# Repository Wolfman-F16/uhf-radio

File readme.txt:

This file is part of uhf-radio.
This project is hosted on github.com/Wolfman-F16
uhf-radio uses v-usb, which comes with its own GPL v2 license (see /usbdrv/license.txt).

    uhf-radio is free software: you can redistribute it and/or modify
    it under the terms of the GNU General Public License as published by
    the Free Software Foundation, either version 2 of the License, or
    any later version.

    uhf-radio is distributed in the hope that it will be useful,
    but WITHOUT ANY WARRANTY; without even the implied warranty of
    MERCHANTABILITY or FITNESS FOR A PARTICULAR PURPOSE.  See the
    GNU General Public License for more details.

    You should have received a copy of the GNU General Public License
    along with uhf-radio.  If not, see <http://www.gnu.org/licenses/>.

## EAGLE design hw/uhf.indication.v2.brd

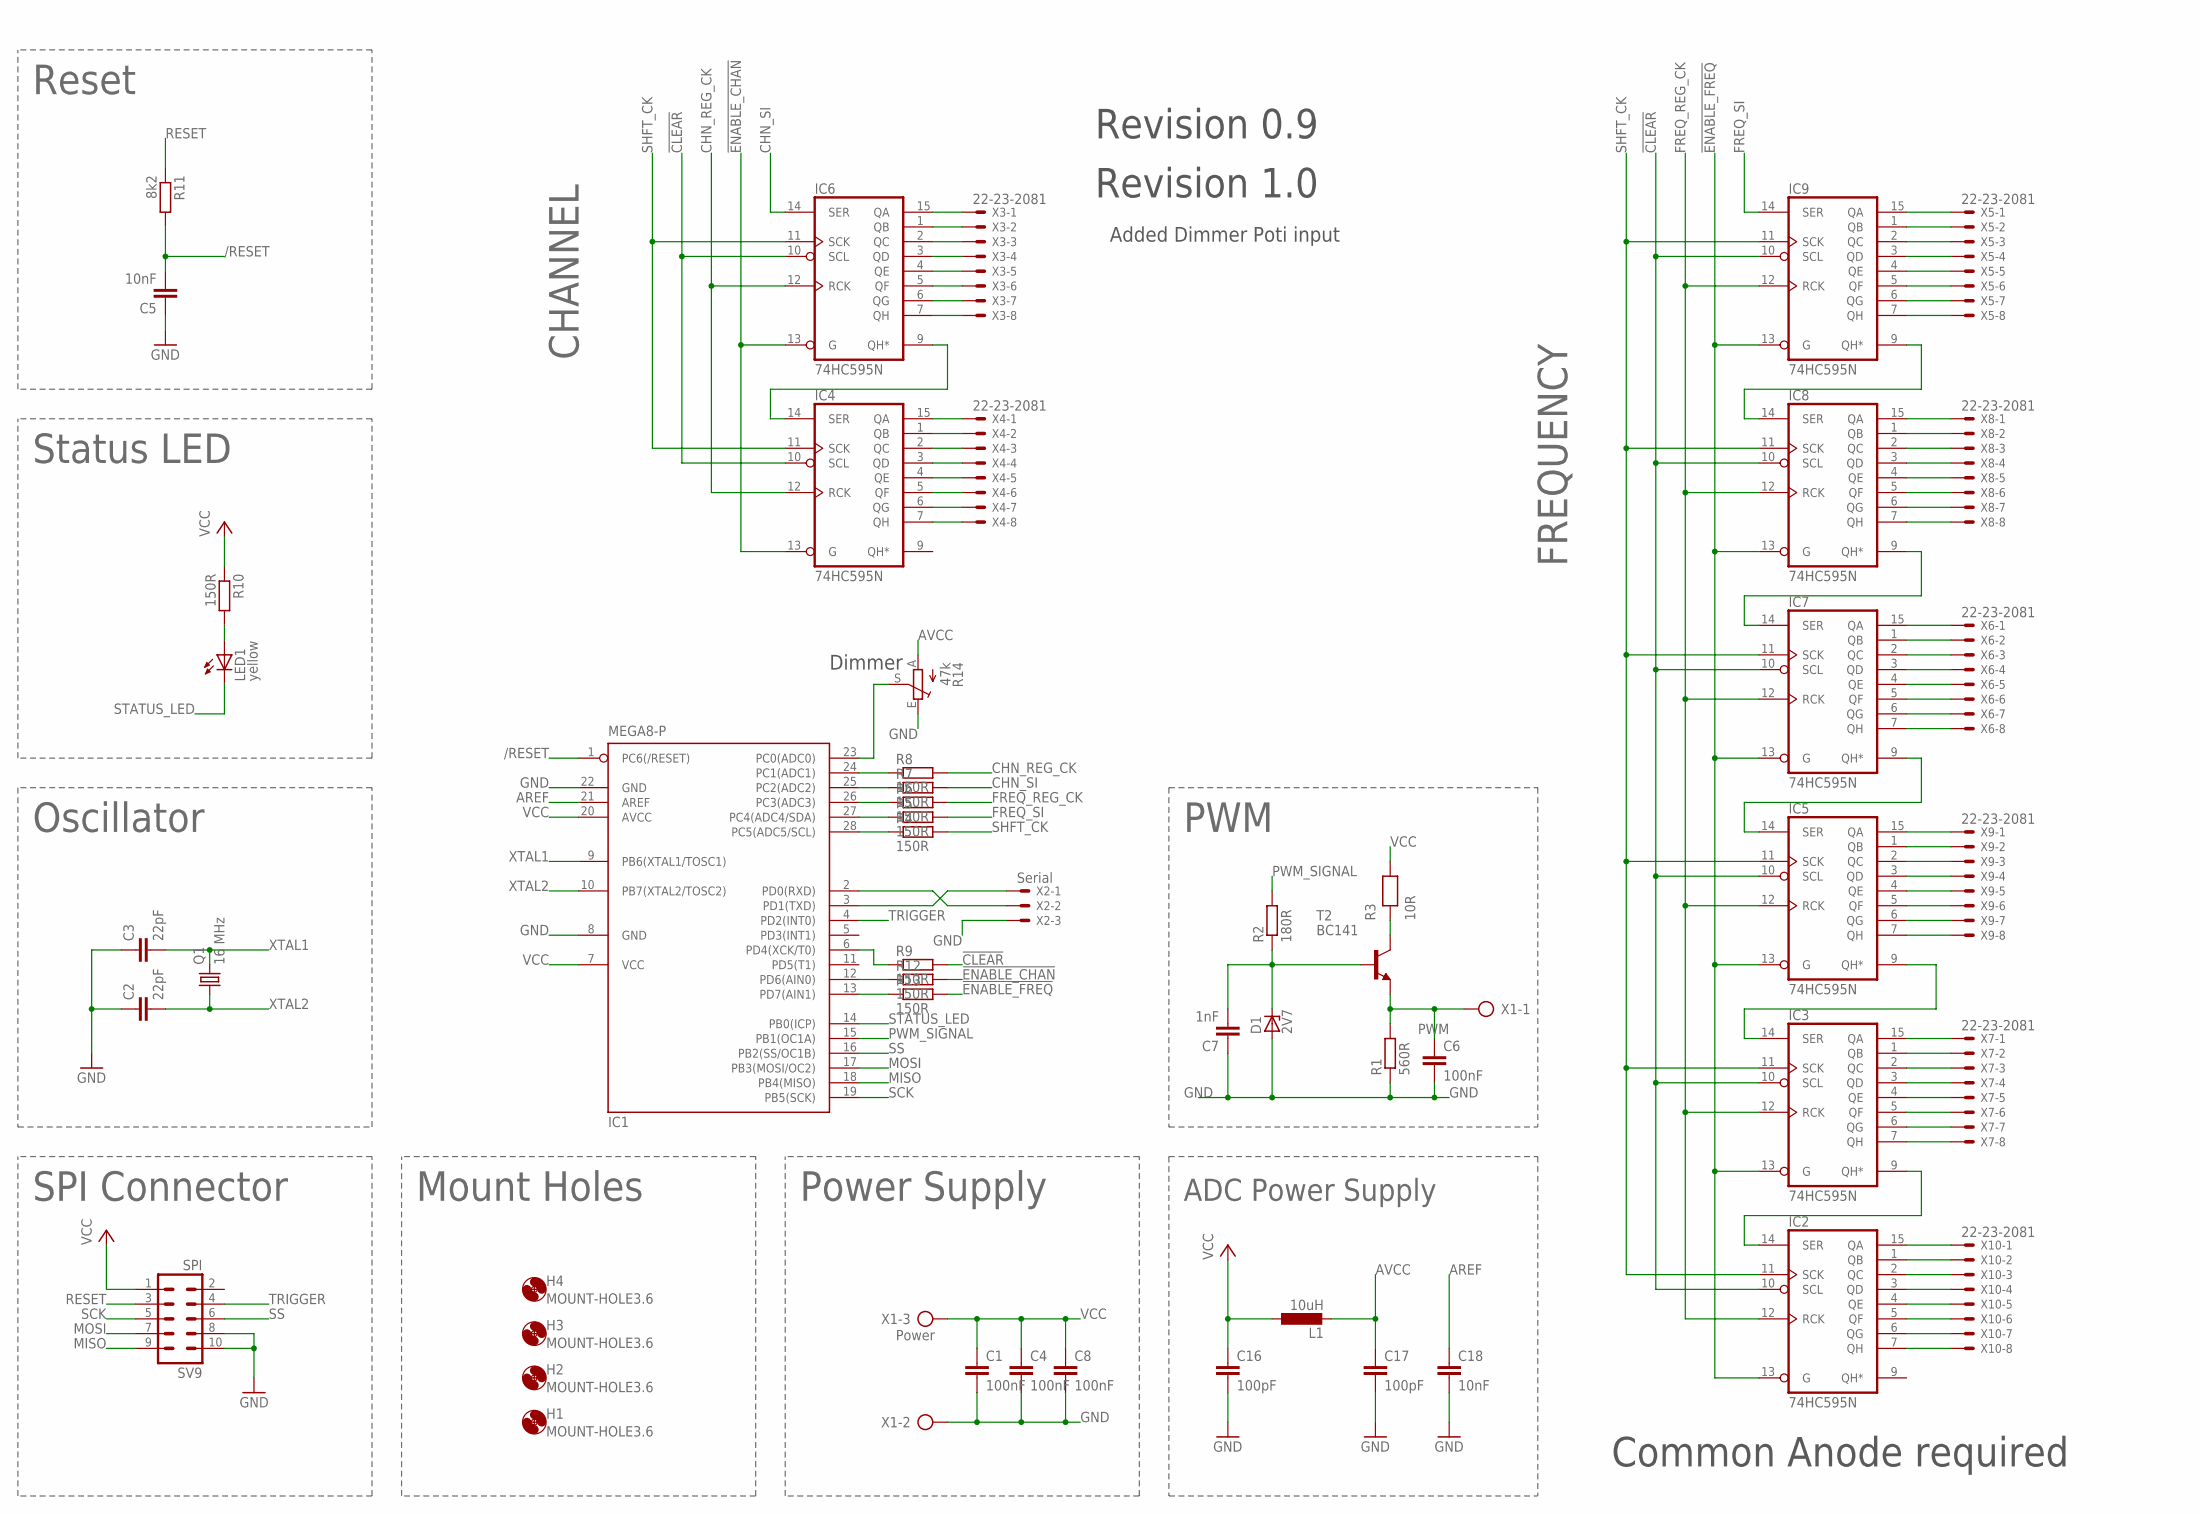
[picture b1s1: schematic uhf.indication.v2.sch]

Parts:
C1, C4, C6, C8: 100nF; C050-024X044
C2, C3: 22pF; C025-025X050
C5, C18: 10nF; C025-025X050
C7: 1nF; C025-025X050
C16, C17: 100pF; C025-025X050
D1: 2V7; ZDIO-10
H1, H2, H3, H4: MOUNT-HOLE3.6; 3,6
IC1: MEGA8-P; DIL28-3
IC2, IC3, IC4, IC5, IC6, IC7, IC8, IC9: 74HC595N; DIL16
L1: 10uH; 2200-15.24
LED1: yellow; CHIPLED_1206
Q1: 16 MHz; HC18U-V
R1: 560R; 0207/2V@1
R2: 180R; 0207/2V@1
R3: 10R; 208-08
R4, R5, R6, R7, R8, R9, R10, R12, R13: 150R; R0805
R11: 8k2; M0805
R14: 47k; B25V
SV9: SPI; ML10
T2: BC141; TO39
X1: Power; AK500/3
X2: Serial; 22-23-2031
X3, X4, X5, X6, X7, X8, X9, X10: 22-23-2081

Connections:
!CLEAR: IC2.10 (SCL), IC3.10 (SCL), IC4.10 (SCL), IC5.10 (SCL), IC6.10 (SCL), IC7.10 (SCL), IC8.10 (SCL), IC9.10 (SCL), R9.2
!ENABLE_CHAN: IC4.13 (G), IC6.13 (G), R12.2
!ENABLE_FREQ: IC2.13 (G), IC3.13 (G), IC5.13 (G), IC7.13 (G), IC8.13 (G), IC9.13 (G), R13.2
/RESET: C5.2, IC1.1 (PC6(/RESET)), R11.2
AREF: C18.1, IC1.21 (AREF)
AVCC: C17.1, L1.2, R14.A
CHN_REG_CK: IC4.12 (RCK), IC6.12 (RCK), R8.2
CHN_SI: IC6.14 (SER), R7.2
FREQ_REG_CK: IC2.12 (RCK), IC3.12 (RCK), IC5.12 (RCK), IC7.12 (RCK), IC8.12 (RCK), IC9.12 (RCK), R6.2
FREQ_SI: IC9.14 (SER), R5.2
GND: C1.2, C2.1, C3.1, C4.2, C5.1, C6.2, C7.1, C8.2, C16.2, C17.2, C18.2, D1.A, IC1.8 (GND), IC1.22 (GND), IC2.8 (GND), IC3.8 (GND), IC4.8 (GND), IC5.8 (GND), IC6.8 (GND), IC7.8 (GND), IC8.8 (GND), IC9.8 (GND), R1.1, R14.E, SV9.8, SV9.10, X1.2, X2.3
MISO: IC1.18 (PB4(MISO)), SV9.9
MOSI: IC1.17 (PB3(MOSI/OC2)), SV9.7
unnamed: IC1.28 (PC5(ADC5/SCL)), R4.1
unnamed: IC1.6 (PD4(XCK/T0)), R9.1
unnamed: IC4.14 (SER), IC6.9 (QH*)
unnamed: IC6.15 (QA), X3.1
unnamed: IC1.24 (PC1(ADC1)), R8.1
unnamed: IC1.25 (PC2(ADC2)), R7.1
unnamed: IC8.14 (SER), IC9.9 (QH*)
unnamed: IC7.14 (SER), IC8.9 (QH*)
unnamed: IC5.14 (SER), IC7.9 (QH*)
unnamed: IC3.14 (SER), IC5.9 (QH*)
unnamed: IC2.14 (SER), IC3.9 (QH*)
unnamed: IC6.1 (QB), X3.2
unnamed: IC6.2 (QC), X3.3
unnamed: IC6.3 (QD), X3.4
unnamed: IC6.4 (QE), X3.5
unnamed: IC6.5 (QF), X3.6
unnamed: IC6.6 (QG), X3.7
unnamed: IC6.7 (QH), X3.8
unnamed: IC4.15 (QA), X4.1
unnamed: IC4.1 (QB), X4.2
unnamed: IC4.2 (QC), X4.3
unnamed: IC4.3 (QD), X4.4
unnamed: IC4.4 (QE), X4.5
unnamed: IC4.5 (QF), X4.6
unnamed: IC4.6 (QG), X4.7
unnamed: IC4.7 (QH), X4.8
unnamed: IC9.15 (QA), X5.1
unnamed: IC9.1 (QB), X5.2
unnamed: IC9.2 (QC), X5.3
unnamed: IC9.3 (QD), X5.4
unnamed: IC9.4 (QE), X5.5
unnamed: IC1.26 (PC3(ADC3)), R6.1
unnamed: IC1.27 (PC4(ADC4/SDA)), R5.1
unnamed: IC9.5 (QF), X5.6
unnamed: IC9.6 (QG), X5.7
unnamed: C7.2, D1.C, R2.1, T2.2 (B)
unnamed: R3.P$2, T2.3 (C)
unnamed: IC1.13 (PD7(AIN1)), R13.1
unnamed: IC1.12 (PD6(AIN0)), R12.1
unnamed: IC1.23 (PC0(ADC0)), R14.S
unnamed: IC9.7 (QH), X5.8
unnamed: IC8.15 (QA), X8.1
unnamed: LED1.A, R10.2
unnamed: IC8.1 (QB), X8.2
unnamed: IC8.2 (QC), X8.3
unnamed: IC8.3 (QD), X8.4
unnamed: IC8.4 (QE), X8.5
unnamed: IC8.5 (QF), X8.6
unnamed: IC8.6 (QG), X8.7
unnamed: IC8.7 (QH), X8.8
unnamed: IC7.15 (QA), X6.1
unnamed: IC7.1 (QB), X6.2
unnamed: IC7.2 (QC), X6.3
unnamed: IC7.3 (QD), X6.4
unnamed: IC7.4 (QE), X6.5
unnamed: IC7.5 (QF), X6.6
unnamed: IC7.6 (QG), X6.7
unnamed: IC7.7 (QH), X6.8
unnamed: IC5.15 (QA), X9.1
unnamed: IC5.1 (QB), X9.2
unnamed: IC5.2 (QC), X9.3
unnamed: IC5.3 (QD), X9.4
unnamed: IC5.4 (QE), X9.5
unnamed: IC5.5 (QF), X9.6
unnamed: IC5.6 (QG), X9.7
unnamed: IC5.7 (QH), X9.8
unnamed: IC3.15 (QA), X7.1
unnamed: IC3.1 (QB), X7.2
unnamed: IC3.2 (QC), X7.3
unnamed: IC3.3 (QD), X7.4
unnamed: IC3.4 (QE), X7.5
unnamed: IC3.5 (QF), X7.6
unnamed: IC3.6 (QG), X7.7
unnamed: IC3.7 (QH), X7.8
unnamed: IC2.15 (QA), X10.1
unnamed: IC2.1 (QB), X10.2
unnamed: IC2.2 (QC), X10.3
unnamed: IC2.3 (QD), X10.4
unnamed: IC2.4 (QE), X10.5
unnamed: IC2.5 (QF), X10.6
unnamed: IC2.6 (QG), X10.7
unnamed: IC2.7 (QH), X10.8
PWM: C6.1, R1.2, T2.1 (E), X1.1
PWM_SIGNAL: IC1.15 (PB1(OC1A)), R2.2
RESET: R11.1, SV9.3
RX: IC1.2 (PD0(RXD)), X2.2
SCK: IC1.19 (PB5(SCK)), SV9.5
SHFT_CK: IC2.11 (SCK), IC3.11 (SCK), IC4.11 (SCK), IC5.11 (SCK), IC6.11 (SCK), IC7.11 (SCK), IC8.11 (SCK), IC9.11 (SCK), R4.2
SS: IC1.16 (PB2(SS/OC1B)), SV9.6
STATUS_LED: IC1.14 (PB0(ICP)), LED1.C
TRIGGER: IC1.4 (PD2(INT0)), SV9.4
TX: IC1.3 (PD1(TXD)), X2.1
VCC: C1.1, C4.1, C8.1, C16.1, IC1.7 (VCC), IC1.20 (AVCC), IC2.16 (VCC), IC3.16 (VCC), IC4.16 (VCC), IC5.16 (VCC), IC6.16 (VCC), IC7.16 (VCC), IC8.16 (VCC), IC9.16 (VCC), L1.1, R3.P$1, R10.1, SV9.1, X1.3
XTAL1: C3.2, IC1.9 (PB6(XTAL1/TOSC1)), Q1.2
XTAL2: C2.2, IC1.10 (PB7(XTAL2/TOSC2)), Q1.1

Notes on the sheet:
SPI Connector
Mount Holes
Oscillator
Status LED
Reset
Power Supply
CHANNEL
FREQUENCY
Common Anode required
PWM
Revision 0.9
Revision 1.0
Added Dimmer Poti input
ADC Power Supply
Dimmer

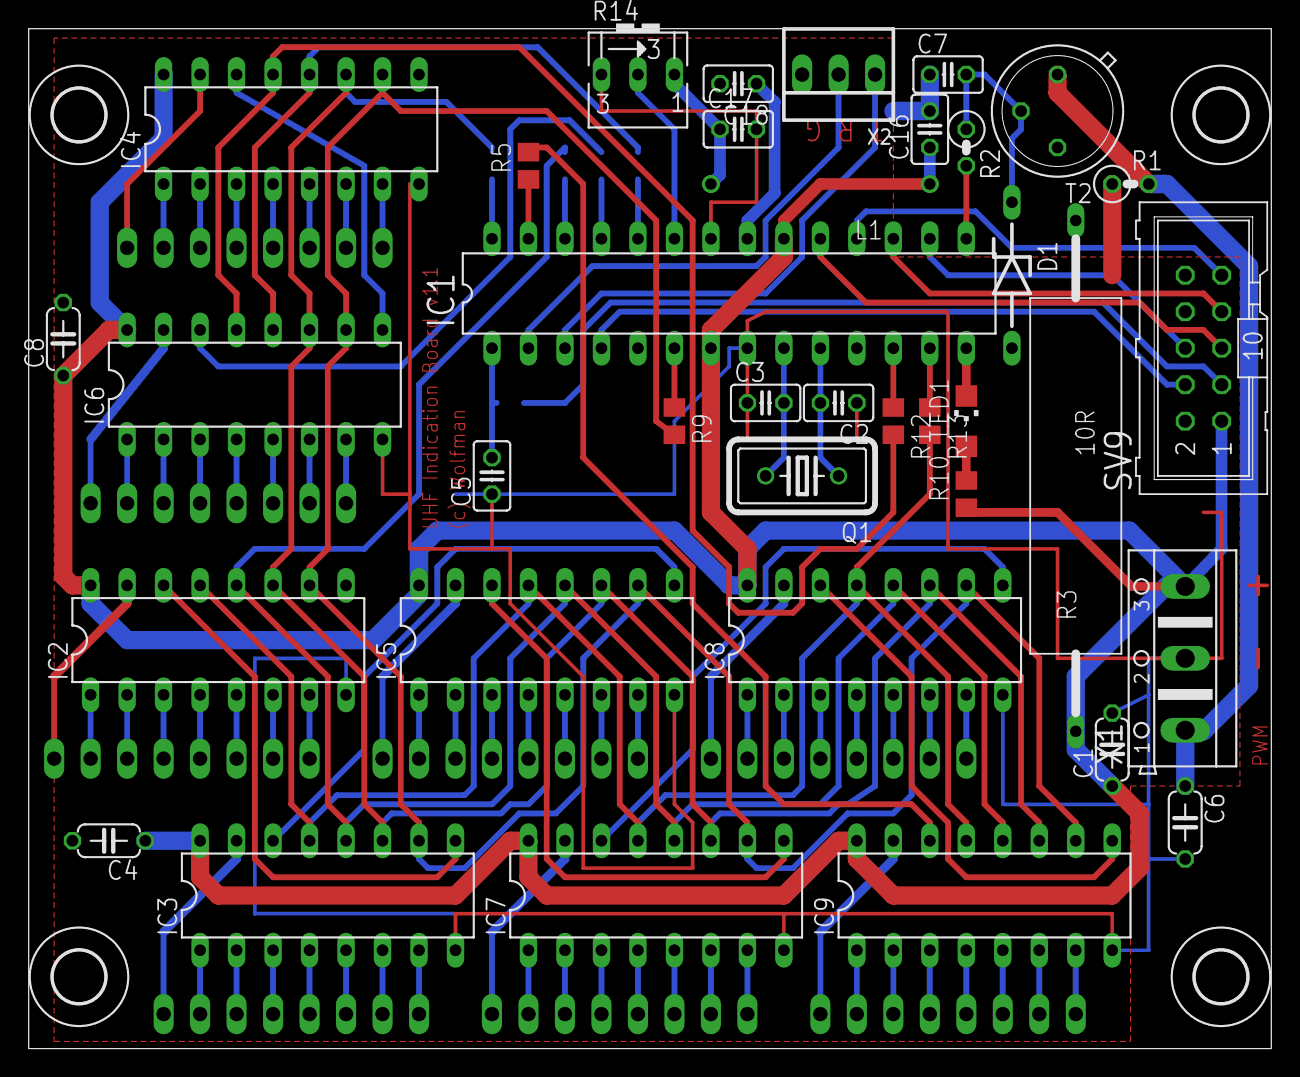
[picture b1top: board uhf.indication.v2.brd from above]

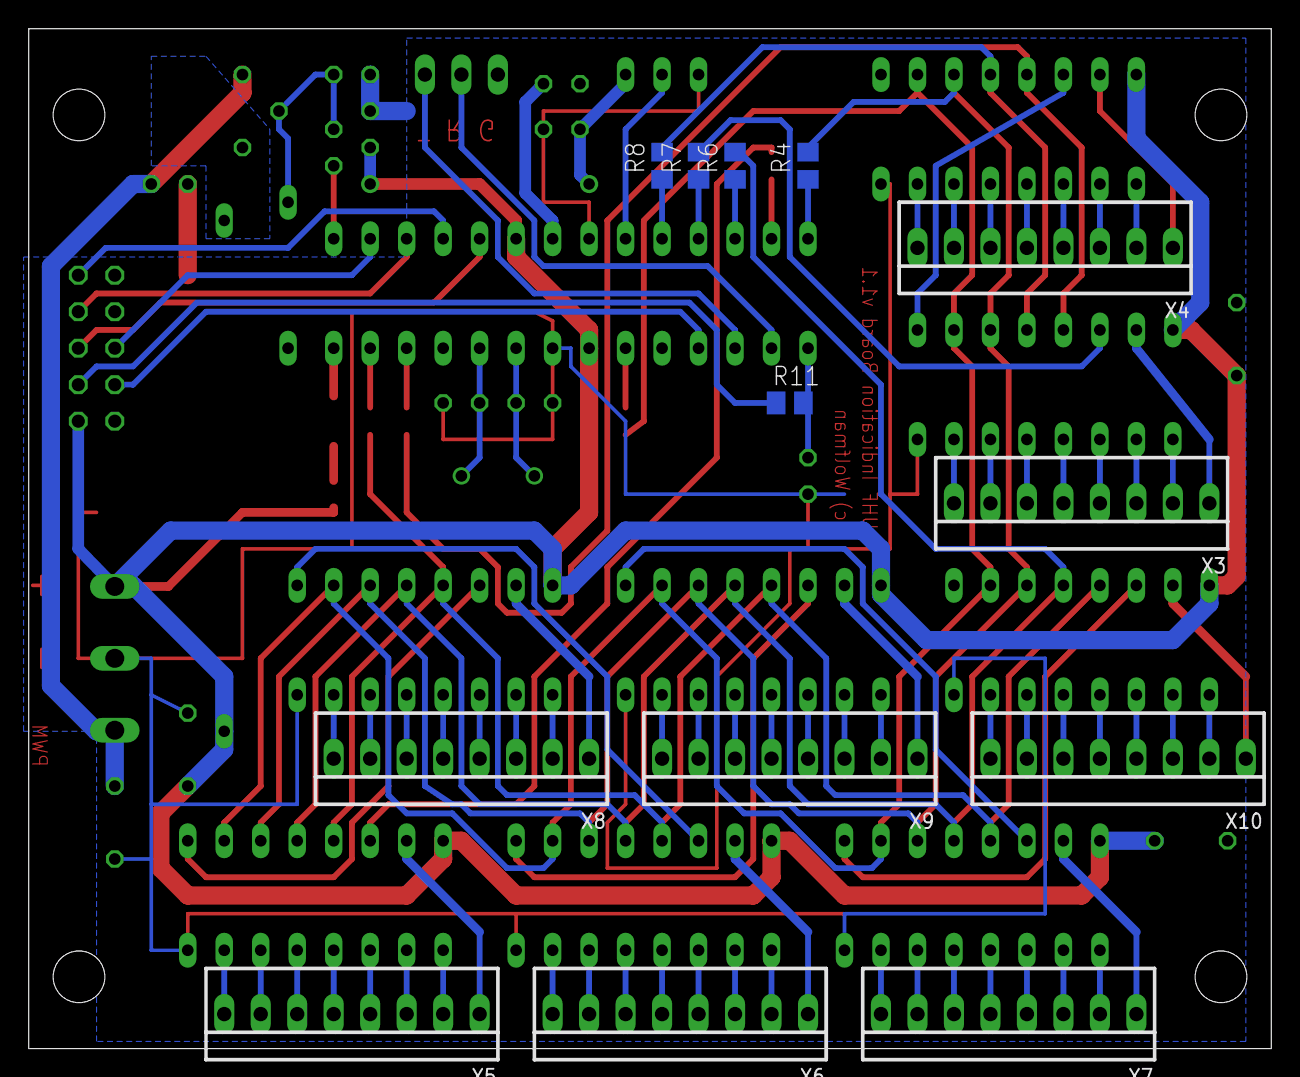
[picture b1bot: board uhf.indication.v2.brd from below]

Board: 2 copper layers, 86.5 x 71.0 mm, 54 parts (13 on the bottom side), 108 nets.

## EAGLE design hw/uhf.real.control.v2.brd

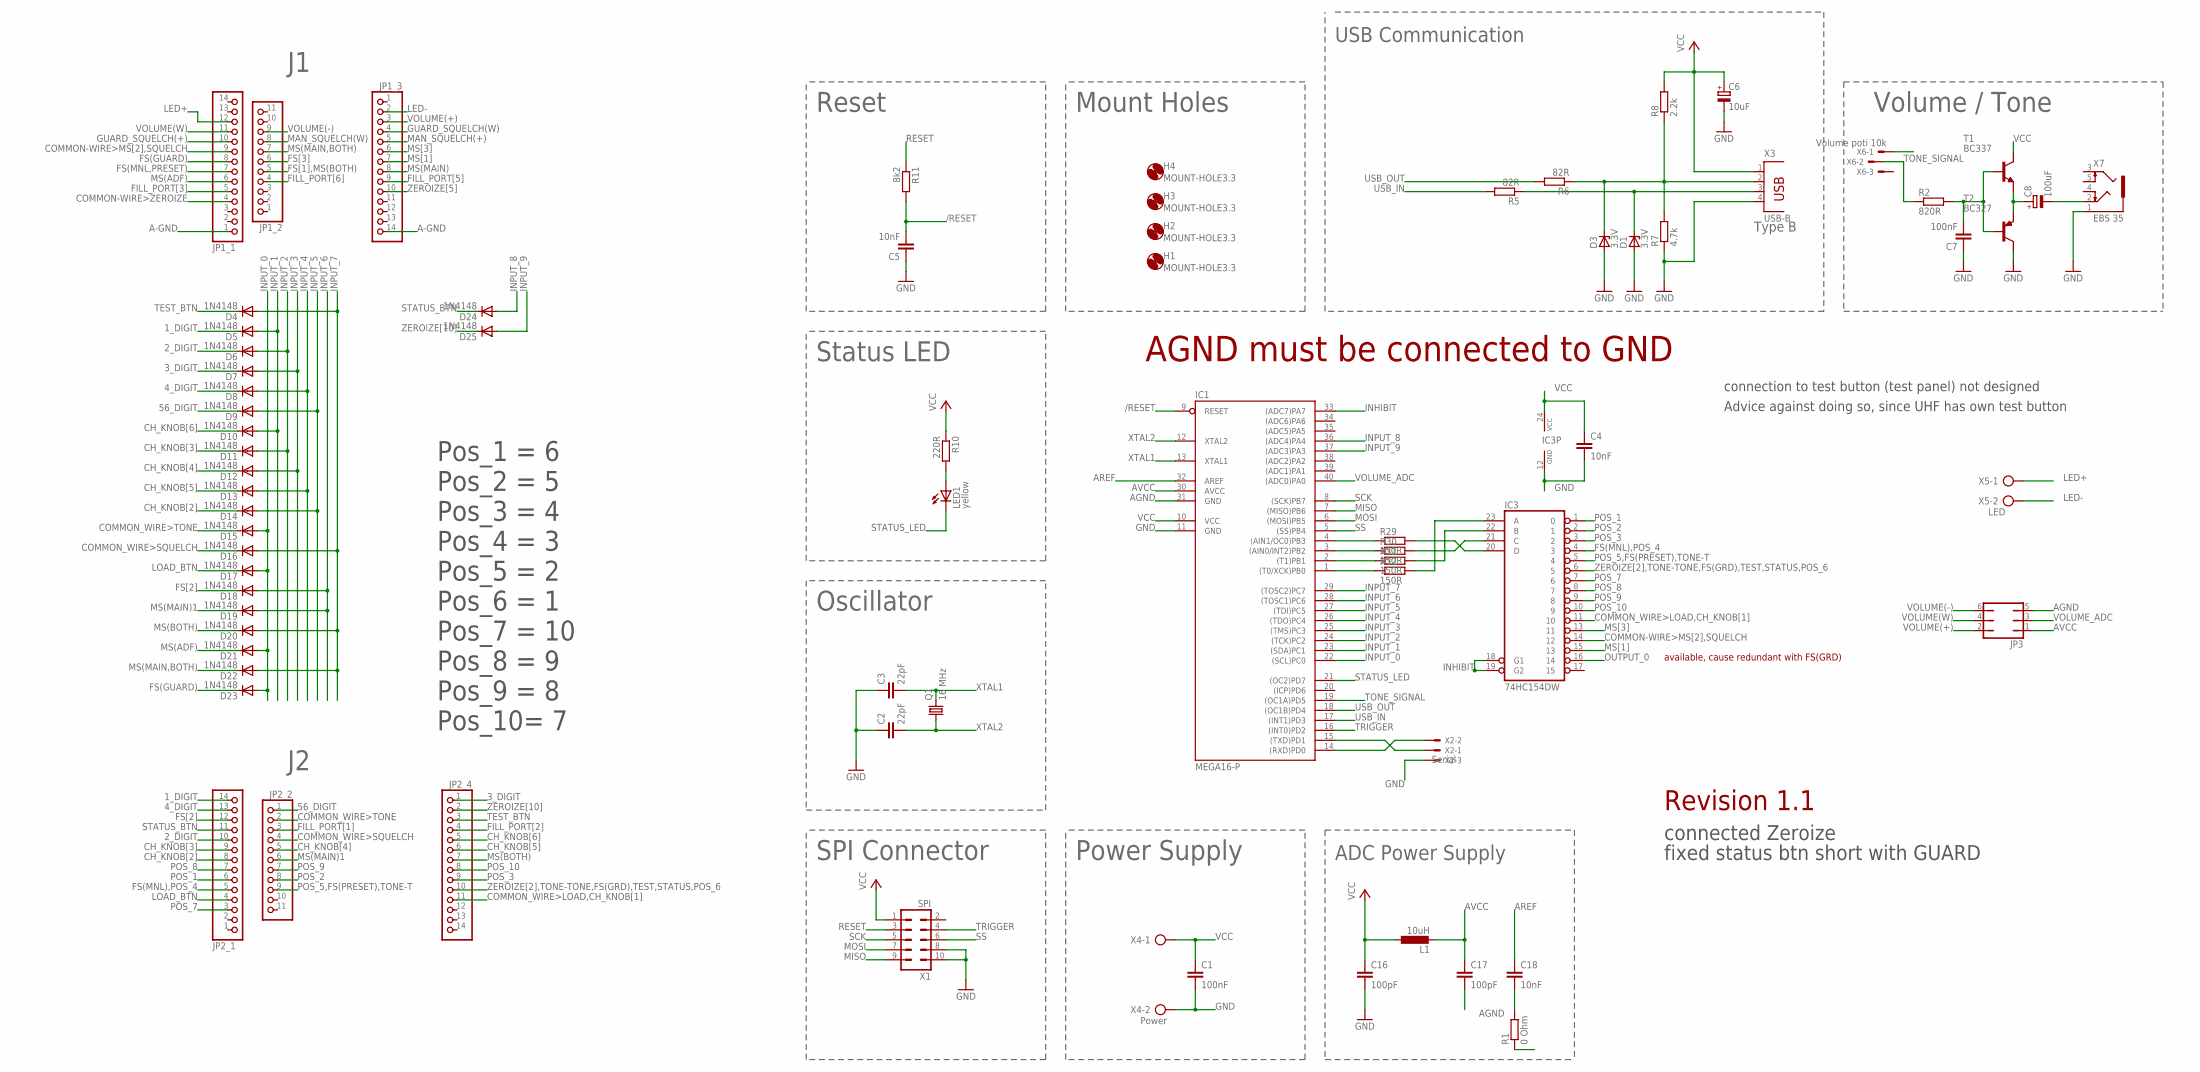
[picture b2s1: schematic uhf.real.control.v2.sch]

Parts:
C1, C7: 100nF; C050-024X044
C2, C3: 22pF; C025-025X050
C4, C5, C18: 10nF; C025-025X050
C6: 10uF; E2,5-6
C8: 100uF; E2,5-6
C16, C17: 100pF; C025-025X050
D1, D3: 3.3V; DO35Z10
D4, D5, D6, D7, D8, D9, D10, D11, D12, D13, D14, D15, D16, D17, D18, D19, D20, D21, D22, D23, D24, D25: 1N4148; MINIMELF
H1, H2, H3, H4: MOUNT-HOLE3.3; 3,3
IC1: MEGA16-P; DIL40
IC3: 74HC154DW; SO24W
JP1_1, JP1_3, JP2_1, JP2_4: PINHD-1X14; 1X14
JP1_2, JP2_2: PINHD-1X11; 1X11
JP3: JP3Q
L1: 10uH; 2200-15.24
LED1: yellow; CHIPLED_1206
Q1: 16 MHz; HC18U-V
R1: 0 Ohm; R0805
R2: 820R; 0207/12
R5, R6: 82R; R0805
R7: 4.7k; R0805
R8: 2.2k; R0805
R10: 220R; R0805
R11: 8k2; M0805
R29, R30, R31, R32: 150R; M0805
T1: BC337; TO92-EBC
T2: BC327; TO92-EBC
X1: SPI; ML10
X2: Serial; 22-23-2031
X3: USB-B; PN61729
X4: Power; AK500/2
X5: LED; AK500/2
X6: Volume poti 10k; 22-23-2031
X7: EBS 35; 1503_09

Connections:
1_DIGIT: D5.C, JP2_1.14
2_DIGIT: D6.C, JP2_1.10
3_DIGIT: D7.C, JP2_4.1
4_DIGIT: D8.C, JP2_1.13
56_DIGIT: D9.C, JP2_2.1
/RESET: C5.2, IC1.9 (RESET), R11.2
A-GND: JP1_1.1, JP1_3.14
AGND: C17.2, C18.2, IC1.31 (GND), JP3.5, R1.2
AREF: C18.1, IC1.32 (AREF)
AVCC: C17.1, IC1.30 (AVCC), JP3.1, L1.2
CH_KNOB[2]: D14.C, JP2_1.8
CH_KNOB[3]: D11.C, JP2_1.9
CH_KNOB[4]: D12.C, JP2_2.5
CH_KNOB[5]: D13.C, JP2_4.6
CH_KNOB[6]: D10.C, JP2_4.5
COMMON-WIRE>MS[2],SQUELCH: IC3.14 (12), JP1_1.9
COMMON-WIRE>ZEROIZE: JP1_1.4
COMMON_WIRE>LOAD,CH_KNOB[1]: IC3.11 (10), JP2_4.11
COMMON_WIRE>SQUELCH: D16.C, JP2_2.4
COMMON_WIRE>TONE: D15.C, JP2_2.2
FILL_PORT[1]: JP2_2.3
FILL_PORT[2]: JP2_4.4
FILL_PORT[3]: JP1_1.5
FILL_PORT[5]: JP1_3.9
FILL_PORT[6]: JP1_2.4
FS(GUARD): D23.C, JP1_1.8
FS(MNL),POS_4: IC3.4 (3), JP2_1.5
FS(MNL,PRESET): JP1_1.7
FS[1],MS(BOTH): JP1_2.5
FS[2]: D18.C, JP2_1.12
FS[3]: JP1_2.6
GND: C1.2, C2.1, C3.1, C4.2, C5.1, C6.-, C7.1, C16.2, D1.A, D3.A, IC1.11 (GND), IC3.12 (GND), R1.1, R7.1, T2.C, X1.8, X1.10, X2.3, X3.4, X4.2, X7.1
GUARD_SQUELCH(+): JP1_1.10
GUARD_SQUELCH(W): JP1_3.4
IN: D1.C, R5.1, X3.3
INHIBIT: IC1.33 ((ADC7)PA7), IC3.18 (G1), IC3.19 (G2)
INPUT_0: D15.A, D17.A, D21.A, D23.A, IC1.22 ((SCL)PC0)
INPUT_1: D5.A, D10.A, IC1.23 ((SDA)PC1)
INPUT_2: D6.A, D11.A, IC1.24 ((TCK)PC2)
INPUT_3: D7.A, D12.A, IC1.25 ((TMS)PC3)
INPUT_4: D8.A, D13.A, IC1.26 ((TDO)PC4)
INPUT_5: D9.A, D14.A, IC1.27 ((TDI)PC5)
INPUT_6: D18.A, D19.A, IC1.28 ((TOSC1)PC6)
INPUT_7: D4.A, D16.A, D20.A, D22.A, IC1.29 ((TOSC2)PC7)
INPUT_8: D24.A, IC1.36 ((ADC4)PA4)
INPUT_9: D25.A, IC1.37 ((ADC3)PA3)
LED+: JP1_1.12, X5.1
LED-: JP1_3.2, X5.2
LOAD_BTN: D17.C, JP2_1.4
MAN_SQUELCH(+): JP1_3.5
MAN_SQUELCH(W): JP1_2.8
MISO: IC1.7 ((MISO)PB6), X1.9
MOSI: IC1.6 ((MOSI)PB5), X1.7
MS(ADF): D21.C, JP1_1.6
MS(BOTH): D20.C, JP2_4.7
MS(MAIN): JP1_3.8
MS(MAIN)1: D19.C, JP2_2.6
MS(MAIN,BOTH): D22.C, JP1_2.7
MS[1]: IC3.15 (13), JP1_3.7
MS[3]: IC3.13 (11), JP1_3.6
unnamed: IC3.23 (A), R32.2
unnamed: C7.2, R2.2, T1.B, T2.B
unnamed: IC3.22 (B), R31.2
unnamed: IC3.21 (C), R30.2
unnamed: C8.+, T1.E, T2.E
unnamed: C8.-, X7.2
unnamed: IC3.20 (D), R29.2
unnamed: IC1.4 ((AIN1/OC0)PB3), R29.1
unnamed: IC1.3 ((AIN0/INT2)PB2), R30.1
unnamed: IC1.2 ((T1)PB1), R31.1
unnamed: IC1.1 ((T0/XCK)PB0), R32.1
unnamed: R2.1, X6.2
unnamed: LED1.A, R10.2
OUT: D3.C, R6.1, R7.2, R8.1, X3.2
OUTPUT_0: IC3.16 (14)
POS_1: IC3.1 (0), JP2_1.6
POS_2: IC3.2 (1), JP2_2.8
POS_3: IC3.3 (2), JP2_4.9
POS_5,FS(PRESET),TONE-T: IC3.5 (4), JP2_2.9
POS_7: IC3.7 (6), JP2_1.3
POS_8: IC3.8 (7), JP2_1.7
POS_9: IC3.9 (8), JP2_2.7
POS_10: IC3.10 (9), JP2_4.8
RESET: R11.1, X1.3
RX: IC1.14 ((RXD)PD0), X2.2
SCK: IC1.8 ((SCK)PB7), X1.5
SS: IC1.5 ((SS)PB4), X1.6
STATUS_BTN: D24.C, JP2_1.11
STATUS_LED: IC1.21 ((OC2)PD7), LED1.C
TEST_BTN: D4.C, JP2_4.3
TONE_SIGNAL: IC1.19 ((OC1A)PD5), X6.1
TRIGGER: IC1.16 ((INT0)PD2), X1.4
TX: IC1.15 ((TXD)PD1), X2.1
USB_IN: IC1.17 ((INT1)PD3), R5.2
USB_OUT: IC1.18 ((OC1B)PD4), R6.2
VCC: C1.1, C4.1, C6.+, C16.1, IC1.10 (VCC), IC3.24 (VCC), L1.1, R8.2, R10.1, T1.C, X1.1, X3.1, X4.1
VOLUME(+): JP1_3.3, JP3.2
VOLUME(-): JP1_2.9, JP3.6
VOLUME(W): JP1_1.11, JP3.4
VOLUME_ADC: IC1.40 ((ADC0)PA0), JP3.3
XTAL1: C3.2, IC1.13 (XTAL1), Q1.2
XTAL2: C2.2, IC1.12 (XTAL2), Q1.1
ZEROIZE[2],TONE-TONE,FS(GRD),TEST,STATUS,POS_6: IC3.6 (5), JP2_4.10
ZEROIZE[5]: JP1_3.10
ZEROIZE[10]: D25.C, JP2_4.2

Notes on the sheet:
SPI Connector
Mount Holes
Oscillator
Status LED
Reset
Power Supply
USB Communication
Type B
Volume / Tone
ADC Power Supply
Pos_1 = 6
Pos_2 = 5
Pos_3 = 4
Pos_4 = 3
Pos_5 = 2
Pos_6 = 1
Pos_7 = 10
Pos_8 = 9
Pos_9 = 8
Pos_10= 7
connected Zeroize
AGND must be connected to GND
connection to test button (test panel) not designed
Advice against doing so, since UHF has own test button
Revision 1.1
fixed status btn short with GUARD
available, cause redundant with FS(GRD)

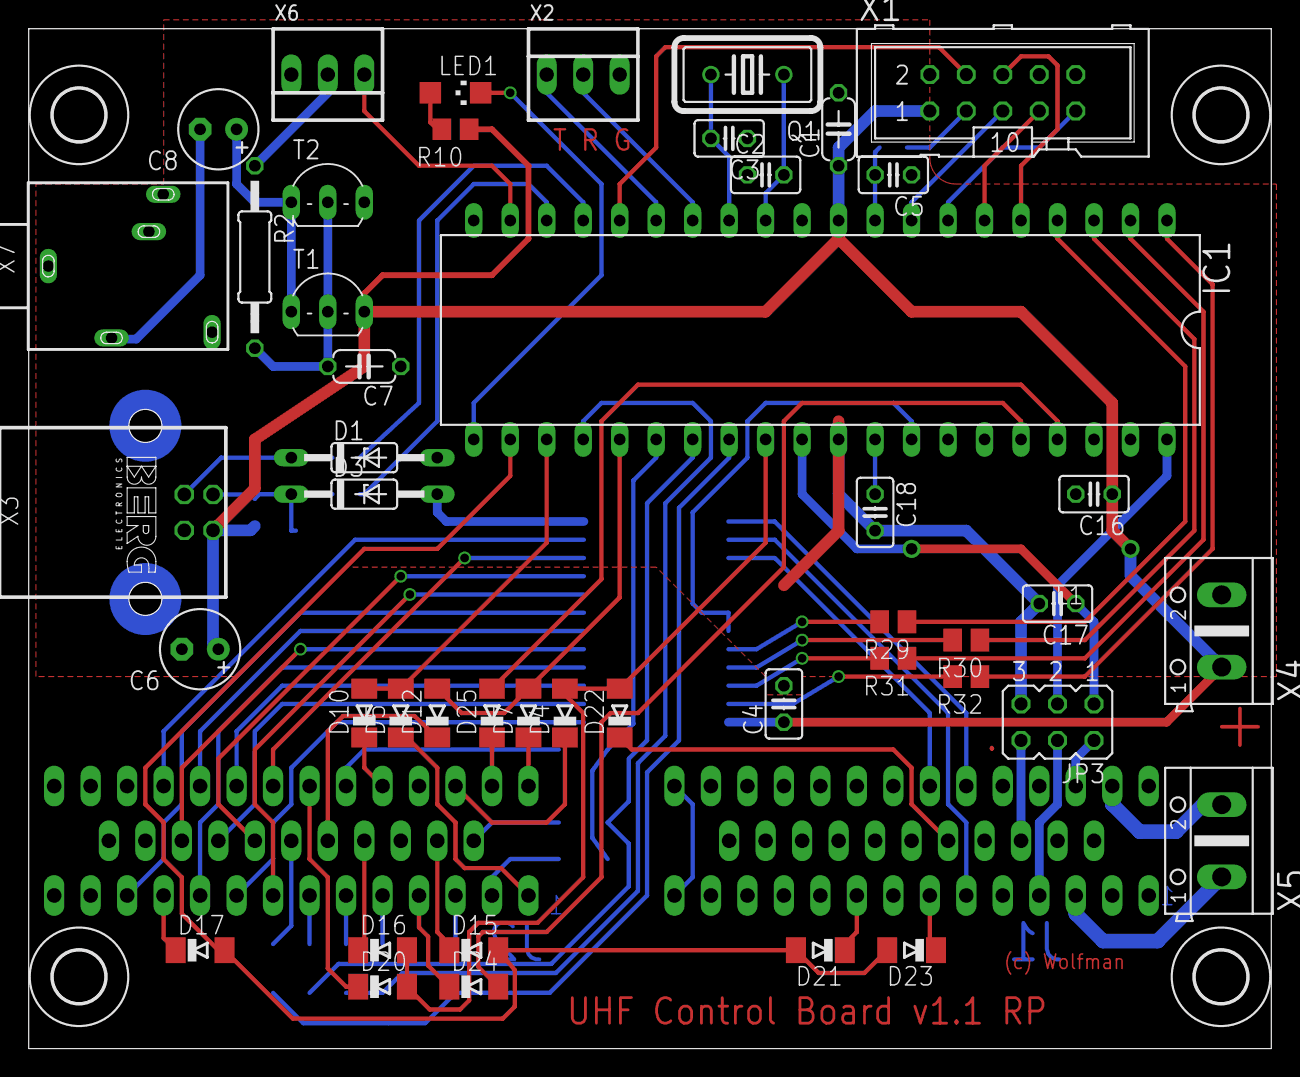
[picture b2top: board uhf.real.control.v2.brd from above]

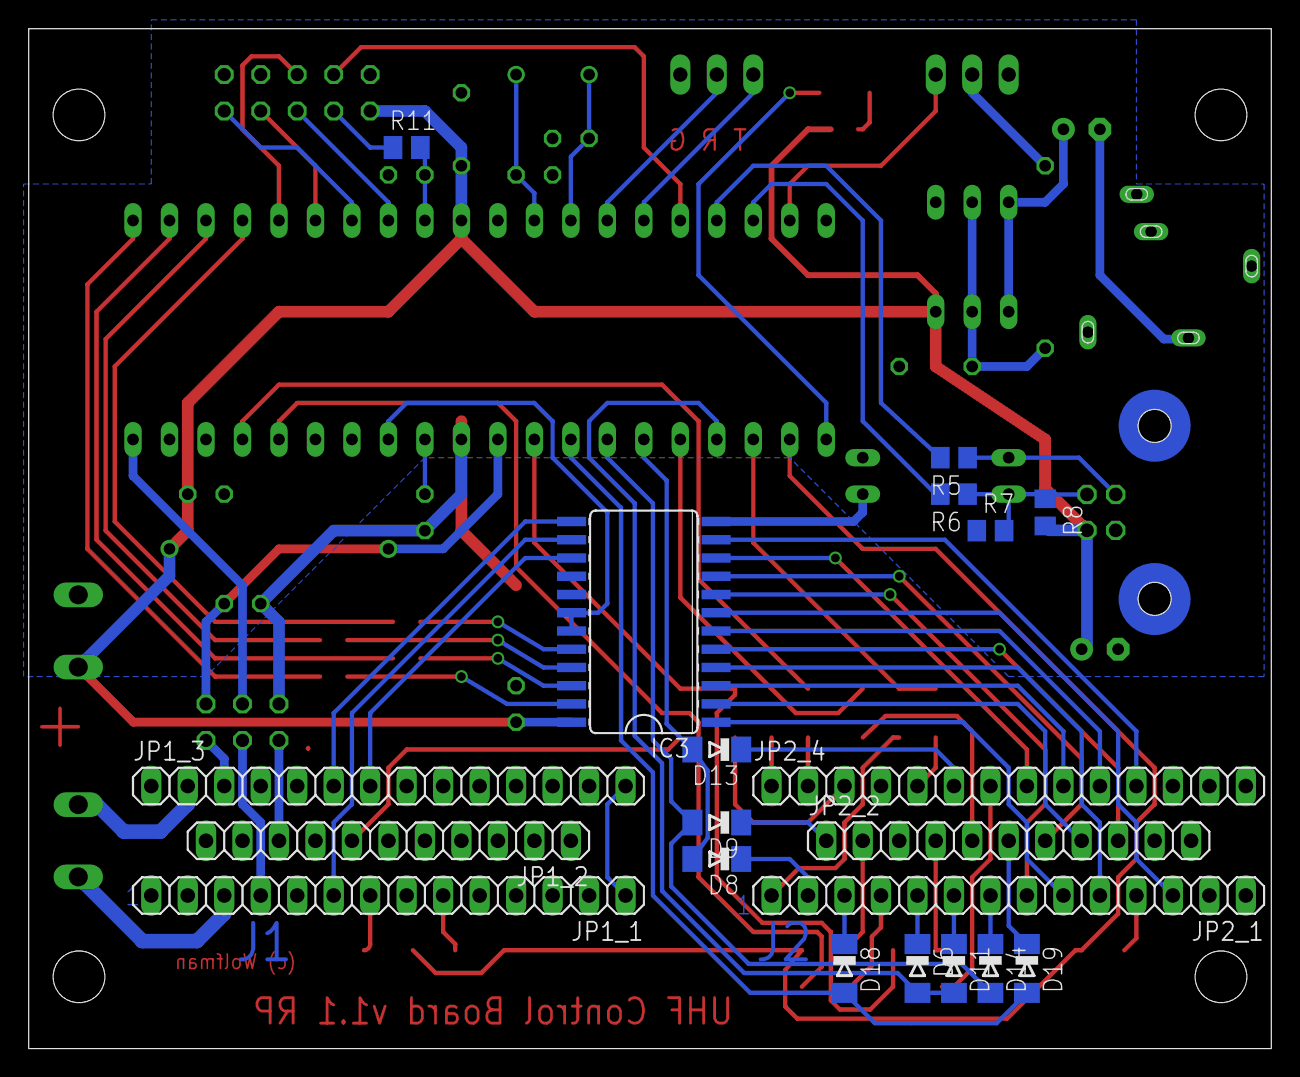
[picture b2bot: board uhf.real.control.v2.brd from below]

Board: 2 copper layers, 86.5 x 71.0 mm, 71 parts (20 on the bottom side), 89 nets.

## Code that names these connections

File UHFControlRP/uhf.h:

/*
 * uhf.h
 *
 *  Created on: 16.04.2011
 *      Author: Wolfgang Engelhard
 *
 * Copyright: (c) 2011 by Wolfgang Engelhard
 * License: GNU GPL v2 (see License.txt)
 */

#ifndef UHF_H_
#define UHF_H_

#include <inttypes.h>

#include "main.h"
#include "timer.h"

/****************************   DEFINITIONS           ************************/
#define INPUT0          PC0
#define INPUT1          PC1
#define INPUT2          PC2
#define INPUT3          PC3
#define INPUT4          PC4
#define INPUT5          PC5
#define INPUT6          PC6
#define INPUT7          PC7
#define INPUT8          PA4
#define INPUT9          PA3

#define COMMON_WIRE_00  0
#define COMMON_WIRE_01  1
#define COMMON_WIRE_02  2
#define COMMON_WIRE_03  3
#define COMMON_WIRE_04  4
#define COMMON_WIRE_05  5
#define COMMON_WIRE_06  6
#define COMMON_WIRE_07  7
#define COMMON_WIRE_08  8
#define COMMON_WIRE_09  9
#define COMMON_WIRE_10  10
#define COMMON_WIRE_11  11
#define COMMON_WIRE_12  12
#define COMMON_WIRE_13  13
#define COMMON_WIRE_14  14
#define COMMON_WIRE_15  15

#define KEY_DDR         DDRC
#define KEY_PORT        PORTC
#define KEY_PIN         PINC
#define KEY_ADD_PIN     PINA
#define KEY0            0
#define KEY1            1
#define KEY2            2
#define KEY3            3
#define KEY4            4
#define KEY5            5
#define KEY6            6
#define KEY7            7

#define ALL_KEYS        (1<<KEY0 | 1<<KEY1 | 1<<KEY2 | 1<<KEY3 | \
                         1<<KEY4 | 1<<KEY5 | 1<<KEY6 | 1<<KEY7 )

#define NR_OF_KEYROWS   16

#define KEY_MASK        ~ALL_KEYS               // key mask must be inverted
#define KEY_ADD_MASK    ~(1<<KEY3 | 1<<KEY4)
#define KEY_ADD_ROW     COMMON_WIRE_05
#define MASK_TEST       0b10000000              // masks test button
#define MASK_SQUELCH		0b10000000              // masks squelch switch
#define MASK_STATUS     0b00010000              // masks status button
#define MASK_UHF_IO			0b10000000
#define MASK_BATTERY    0b00000010
#define MASK_BACKUP     0b00000001

#define REPEAT_MASK     (1<<KEY0)               // repeat: key0 (test)
#define REPEAT_START    50                      // after 500ms
#define REPEAT_NEXT     20                      // every 200ms
#define MASK_CH_01      0b00000010
#define MASK_CH_02      0b00000110
#define MASK_CH_03      0b00000100
#define MASK_CH_04      0b00001100
#define MASK_CH_05      0b00001110
#define MASK_CH_06      0b00001010
#define MASK_CH_07      0b00001000
#define MASK_CH_08      0b00011000
#define MASK_CH_09      0b00011010
#define MASK_CH_10      0b00011110
#define MASK_CH_11      0b00011100
#define MASK_CH_12      0b00010100
#define MASK_CH_13      0b00010110
#define MASK_CH_14      0b00010010
#define MASK_CH_15      0b00010000
#define MASK_CH_16      0b00110000
#define MASK_CH_17      0b00110010
#define MASK_CH_18      0b00110110
#define MASK_CH_19      0b00110100
#define MASK_CH_20      0b00111100
#define MASK_CHANNEL	(MASK_CH_20 | MASK_CH_01)

#define MAX_CHANNELS    20
#define CHAN_ARRAY_SIZE 1
#define FREQ_ARRAY_SIZE 6

#define  SPI_SOF        0x1A
//0x1A
#define  SPI_EOF        0xA5
//0xA5

#define MAX_MWOD 	6
#define MAX_FMT 	16
#define MAX_DOM 	2

#define eeUhfState eePresetFrequencies[MAX_CHANNELS][FREQ_ARRAY_SIZE]
#define eeMnlFreq  eePresetFrequencies[MAX_CHANNELS]

/****************************   Structures      *******************************/
/**
 * display content
 */
typedef struct {
	uint8_t channel;
	uint8_t frequency[FREQ_ARRAY_SIZE];
} radio_t;

/**
 * MPG switch status
 */
typedef struct {
	unsigned FUSEL :3;
	unsigned OFF :1;
	unsigned MODE :3;
	unsigned BACKUP :1;
} uhfKeyState_t;

/**
 * uhf control structure
 */
typedef struct {
	unsigned audio :3;
	unsigned audioCycle :3;

	unsigned test :1;
	unsigned squelch :1;

	unsigned invalidSWOD :3;
	unsigned gotTone :1;
	unsigned ch20 :1;

	unsigned resend :1;
	unsigned firstRun :1;
	unsigned fmtTimeout :1;
} uhfControl_t;

/**
 * MWOD structure used for ring buffer
 */
typedef struct {
	uint8_t ch_20[FREQ_ARRAY_SIZE];
	uint8_t ch_19[FREQ_ARRAY_SIZE];
	uint8_t ch_18[FREQ_ARRAY_SIZE];
	uint8_t ch_17[FREQ_ARRAY_SIZE];

	uint8_t ch_16[FREQ_ARRAY_SIZE];
	uint8_t ch_15[FREQ_ARRAY_SIZE];
	uint8_t ch_14[2];
} uhf_wod_t;

/**
 * fmt change
 */
typedef struct {
	uint8_t ch[MAX_FMT][FREQ_ARRAY_SIZE];
} uhf_fmt_t;

/****************************   ENUMS           *******************************/
typedef enum {
	VEROP, MLOAD, ERASE, FMTCHG, DISP_OFF
} uhfOpMode_e;

typedef enum {
	BEEP, WAVE, PULSE, TOD, DOUBLE, WARN
} tone_e;

typedef enum {
	FS_MNL, FS_PRESET, FS_GUARD
} functionSelector_e;

enum modeSelector_e {
	MS_OFF, MS_ADF, MS_MAIN, MS_BOTH
};

enum offSelector_e {
	MS_ON = 1
};

/****************************   GLOBAL VARIABLES ******************************/
// extern eeprom variables
extern const 	uint8_t 			eePresetFrequencies[MAX_CHANNELS][FREQ_ARRAY_SIZE];
// extern variables
extern 				uhfKeyState_t uhfKeyState;
extern 				uhfOpMode_e		uhfOpMode;
extern const	uint8_t 	 	 *uhfStatusStrings[];
extern 			 	uhf_wod_t   	uhfMWOD[];
extern 				uint8_t 			currMWodIndex;
extern 			 	uhf_wod_t   	uhfSWOD;
extern				uhf_fmt_t 		uhfFMT;
extern const 	uint8_t 			eeFmtNets[MAX_FMT][FREQ_ARRAY_SIZE];
extern 			 	uint8_t 			currDayOfMonth[]; // current day of month
extern 				radio_t 			radio;

// ISR values
extern volatile uhfControl_t 	uhfControl;
static volatile uint8_t 			upperByte;

/****************************   FUNCTION DECLARATIONS *************************/
void processInputData(uint8_t);
void processChannel(void);
void display(uhfOpMode_e);
void playTone(tone_e);

void initVariables(void);
void sendData(uint8_t*, uint8_t*);

void eraseMWOD(void);

void setManual(void);
void setPreset(void);
void setGuard(void);

void setTest(void);
void setLoad(void);
void setStatus(void);

void setToneT(void);
void setToneTone(void);

void setMain(void);
void setBoth(void);
void setAdf(void);
void setUhfOn(void);
void setUhfOff(void);

void goActive(void);

void checkDom(void);

void forcedReadUhfState(void);
void forcedReadFreq(void);

uint8_t* getChannelString(void);
uint8_t* getFrequencyString(void);

/****************************   Inline Functions      *************************/
static inline void isrTimer1() {
	// not used during audio output
	TCCR1B = 0;
	uhfControl.test = FALSE;
	uhfControl.resend = TRUE;
#ifdef deactivated
	uhfControl.fmtTimeout = TRUE;
#endif
}

static inline void isrTimer2() {

	if (upperByte > 0) {
		upperByte--;
	} else {
		// test type of tone to be played
		// if beep then this
		if (uhfControl.audio == BEEP) {
			TCCR2 = 0;
			disablePWM1A();
		}
		/* TOD */
		if (uhfControl.audio == TOD) {
			setT1Pwm(FREQ_1KHZ);
			enablePWM1A();
			setT2Delay(ONE_SEC);
			uhfControl.audio = BEEP;
		}
		/* wave  */
		if (uhfControl.audio == WAVE) {
			switch (uhfControl.audioCycle) {
			case 3:
			case 1:
				setT1Pwm(FREQ_1KHZ);
				enablePWM1A();
				setT2Delay(ONE_SEC);
				uhfControl.audioCycle--;
				break;
			case 2:
				setT1Pwm(FREQ_500HZ);
				enablePWM1A();
				setT2Delay(ONE_SEC);
				uhfControl.audioCycle--;
				break;
			default:
				TCCR2 = 0;
				disablePWM1A();
				break;

			}
		}
		/* double beep */
		if(uhfControl.audio == DOUBLE) {
			switch(uhfControl.audioCycle) {
			case 2:
				disablePWM1A();
				setT2Delay(ONE_SEC);
				uhfControl.audioCycle--;
				break;
			case 1:
				setT1Pwm(FREQ_1KHZ);
				enablePWM1A();
				setT2Delay(ONE_SEC);
				uhfControl.audioCycle--;
				break;
			default:
				TCCR2 = 0;
				disablePWM1A();
				break;
			}
		}
		/* pulse */
		if (uhfControl.audio == PULSE) {
			switch (uhfControl.audioCycle) {
			case 4:
			case 2:
				// no sound for one sec
				disablePWM1A();
				setT2Delay(HALF_SEC);
				uhfControl.audioCycle--;
				break;
			case 3:
			case 1:
				setT1Pwm(FREQ_1KHZ);
				enablePWM1A();
				setT2Delay(HALF_SEC);
				uhfControl.audioCycle--;
				break;
			default:
				TCCR2 = 0;
				disablePWM1A();
				break;
			}
		}
	}
}

static inline void isrAdc() {
	;
}

#endif /* UHF_H_ */

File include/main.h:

/*
 * main.h
 *
 *  Created on: 16.04.2011
 *      Author: Wolfgang Engelhard
 *
 * Copyright: (c) 2011 by Wolfgang Engelhard
 * License: GNU GPL v2 (see License.txt)
 */

#ifndef MAIN_H_
#define MAIN_H_

#include <avr/io.h>

/****************************   DEFINITIONS           ************************/
#define TRUE    1
#define FALSE   0

#define STATUS_LED_PORT PORTD
#define MULTIPLEXPORT   PORTB

#define PIN_INHIBIT     PORTA7
#define PIN_OUTPUT_0    PORTA6
#define PIN_WAVEOUT     PORTD5
#define PIN_LED         PORTD7
#define PIN_UART_TX     PORTD1
#define PIN_TRIGGER     PORTD2
#define SPI_MOSI        PORTB5
#define SPI_SCK         PORTB7
#define SPI_SS          PORTB4

/****************************   INLINE FUNCTIONS      ************************/
static inline void setStatusLedOff(void) {
  STATUS_LED_PORT |= (1 << PIN_LED);
}

static inline void setStatusLedOn(void) {
  STATUS_LED_PORT &= ~(1 << PIN_LED);
}

#endif /* MAIN_H_ */

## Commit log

2011-10-30 Initial submit.
2015-12-13 Licensed under GPLv2.
    Special thanks to joonas pihlajamaa, he was a great help with this
    project.
    initial commit for github
2015-12-14 re-added documentation and eagle brd files
2015-12-14 added firmware files for indication board
2015-12-29 added additional keys
    applied formatting
2015-12-29 added hex file of new version (24)
2015-12-30 added bom errata
2016-01-16 added updated documentation
2016-04-10 added implementation to send preset frequencies via usb
    usb message protocol now supports preset frequencies (0xEE)
    fixed FMT NET eeprom write
2016-05-16 added firmware binary of version 0025 (ae8af33)
2018-11-18 added channel blanking.
    Channel display is now blanked when in MNL or GUARD function.
    Version is now 26
    build is now always cleaning before hand
    refactored some comments
2018-11-25 added firmware v26 hex binary
2018-12-29 added schematics for board files
2019-04-29 update and fix of mapped keys send to PC. Synced with BMS 4.34.
2021-03-07 Update of keys to BMS 4.35 U1
2021-03-07 replaced incorrect .hex file with current version v28
2021-03-07 Update of UHF Quickstart document.
2021-03-07 removed old document versions.
